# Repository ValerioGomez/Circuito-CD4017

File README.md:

# Circuito-CD4017
Encender Apagar Foco con aplausos

- 1 resistencia de 10k (R1)
- 1 resistencia de 100k (R2)
- 4 resistencias de 1k (R3, R4, R5, R7)
- 1 resistencia de 330 ohm. (R6)
- 2 transistores NPN 2N2222A (Q1 Y Q2)
- 1 potenciómetro de 100k.
- 1 micro pequeño.
- 1 condensador electrolítico de 47uF /16v.(C1)
- 1 diodo led. (D1)
- 1 diodo rectificador 1N1004. (D2)
- 1 circuito integrado NE555 (U1)
- 1 circuito integrado CD4017 (U2)
- 1 relé de 220v AC / 6v DC ( si en su país de 110v AC reemplázalo el relé por uno de 110v AC / 6v DC)
- 1 lámpara de 220v AC (va conectado al relé para la etapa de potencia)
- Fuente de 5v DC.

>

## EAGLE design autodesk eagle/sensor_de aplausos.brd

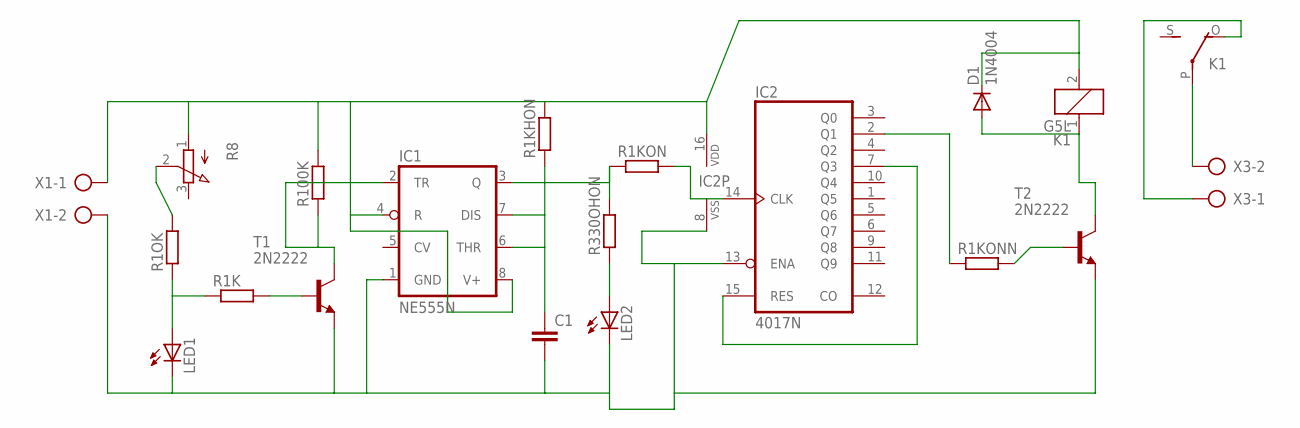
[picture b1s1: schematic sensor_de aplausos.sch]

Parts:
C1: C5/5; C5B5
D1: 1N4004; DO41-10
IC1: NE555N; DIL08
IC2: 4017N; DIL16
K1: G5L; G5LE
LED1, LED2: LED5MM
R1K, R1KHON, R1KON, R1KONN, R1OK, R100K, R330OHON: R-EU_0207/12; 0207/12
R8: 3RP/1610N
T1, T2: 2N2222; TO18
X1, X3: AK300/2

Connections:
unnamed: K1.P, X3.2
unnamed: R1OK.2, R8.2 (S)
unnamed: D1.C, IC1.4 (R), IC1.8 (V+), IC2.16 (VDD), K1.2, R1KHON.2, R8.1 (A), R100K.2, X1.1
unnamed: LED1.A, R1K.1, R1OK.1
unnamed: IC1.2 (TR), R100K.1, T1.3 (C)
unnamed: R1K.2, T1.2 (B)
unnamed: K1.O, X3.1
unnamed: C1.1, IC1.6 (THR), IC1.7 (DIS), R1KHON.1
unnamed: IC2.2 (Q1), R1KONN.1
unnamed: D1.A, K1.1, T2.3 (C)
unnamed: IC1.3 (Q), R1KON.1, R330OHON.2
unnamed: LED2.A, R330OHON.1
unnamed: R1KONN.2, T2.2 (B)
unnamed: IC2.14 (CLK), R1KON.2
unnamed: IC2.7 (Q3), IC2.15 (RES)
unnamed: C1.2, IC1.1 (GND), IC2.8 (VSS), IC2.13 (ENA), LED1.K (C), LED2.K (C), T1.1 (E), T2.1 (E), X1.2

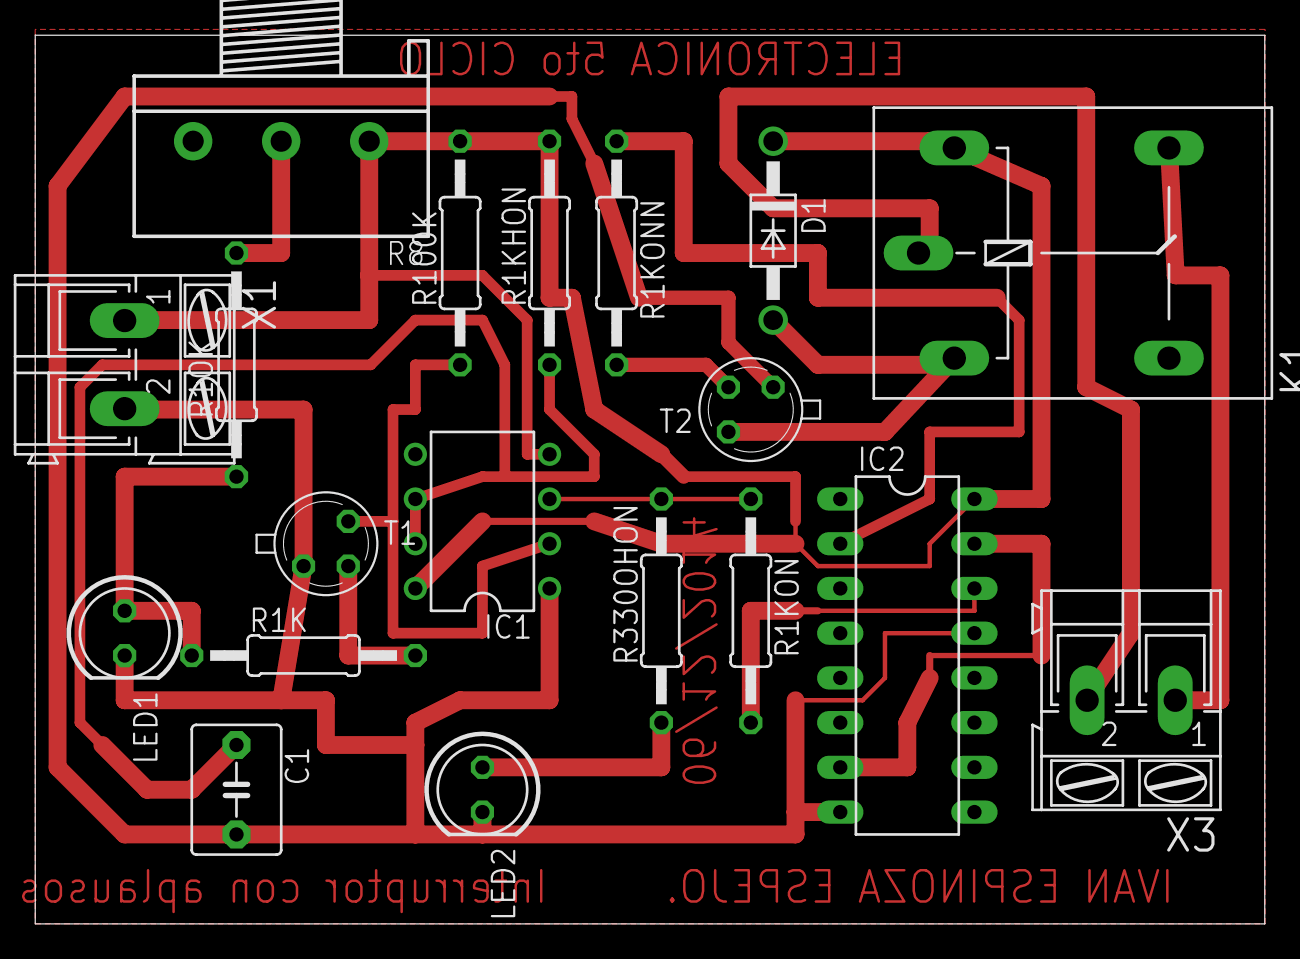
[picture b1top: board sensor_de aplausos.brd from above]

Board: 2 copper layers, 69.8 x 50.5 mm, 19 parts (0 on the bottom side), 16 nets.

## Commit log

2022-05-20 finalizando
    culminando tareas
2022-05-20 actualziando
2022-05-20 baquelita
2022-05-20 imagen
